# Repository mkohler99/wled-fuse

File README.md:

# wled-fuse
# WTF?
Happy holidays, If you're reading this the odds are you received one of my um, holiday cards? and have scanned the QR code on the back. This is some documentation for how to use WLED specifically in the context of this board.

# About WLED
WLED Is an open source RGB Pixel LED controller made by smart people on the internet. Information about the WLED project can be found here: [WLED Github Page](https://github.com/Aircoookie/WLED)
I make no claims about the reliability or color accuracy of WLED, however I think it's a really neat project and saved me having to even think about the software for this project (no thoughts, head empty, just solder LED and exist). WLED has some neat features that make it great for making fun LED toys. In no particular order:

 - Wifi Control with built in Web GUI
 - Built in controls and effects
 - Support for sACN (Referred to as E 1.31 for some reason)
 - Automatic wifi setup 

# How to connect
When the device boots, it attempts to connect to its last known wifi network. In most cases, when you first power up your board, it will not connect automatically. In this case, the board will create its own hotspot with the SSID **WLED-FUSE** 

in order to connect to the onboard hotspot, you will need to enter the default WLED password, **wled1234** you should then be automatically redirected to the WLED GUI which self hosts at **4.3.2.1** (which is a bit of a strange vanity IP, but I guess since they are the router they can do whatever they want)

You can use the device like this with its built in AP mode, but your phone may be weird about being connected to wifi that doesn't go anywhere, so you may want to connect the board to a real wifi network. 

# Wifi Setup

### To connect your WLED module to your home Wifi:

**1.**  Click on the  _Config_  (gear) icon to edit your WLED module settings and choose 'Wifi Setup'.

**2.**  For most home networks, simply enter your Wifi network's name and network password. You can also change the mDNS address for your WLED module here. By default, I've made it **fuse.local** so once your device is connected, you should just be able to enter that into your browser and you're off to the races. You can also 'Scan' for available networks and enter the password to any you find.

**3.**  Click Save & Connect at the top of the page.

**4.**  Reconnect your device to your home's Wifi network.

**5.**  Check the device list in your router's user interface for the IP of the WLED device within your local network. Alternatively, the device will advertise itself with mDNS as **fuse.local** so in theory, just enter that in your address bar and it should take you to the GUI. Failing that, use the WLED app (free on the App Store, as it is able to discover WLED boards without knowing the IP! Have fun with the WLED software!

# WLED Tips:
**1** Whatever is saved into preset 1 will load on boot, making the board's power up preset / effect customizable. 

**2** A visual list of WLED's built in FX can be found [here](https://kno.wled.ge/features/effects/)

**3** Multiple WLED boards can be synchronized together

# DMX Control
WLED is controllable using Artnet or Streaming ACN. Information on how to do that can be found [in the WLED documentation](https://kno.wled.ge/interfaces/e1.31-dmx/) Someone should make a DMX screen in d3 that implements its pixel map so it can be mapped from d3.

# WLED on your own
If you want to install WLED fresh, you can connect your board over USB-C to a computer and reinstall WLED from [this website](https://install.wled.me) which uses 'Web Serial' (which is a real web API for communicating with locally plugged in serial devices) to reprogram the board. It's WILD how easy they made this process. 

After flashing, only the 'F' will light up because WLED does not know about the other GPIO pins I used in my custom layout. As an exercise, I broke each letter out into its own 'pin' off the microcontroller [(Schematic for those interested)](https://github.com/mkohler99/wled-fuse/blob/main/Electronics/Drawings/Fuse%20LED%20Board%20Schematic.pdf), so in the LED settings you'll need to set up the following LED outputs:

 1. Pin 16 - 10 LEDs - Type WS281X - GRB
 2. Pin 17 - 10 LEDs - Type WS281X - GRB
 3. Pin 18 - 10 LEDs - Type WS281X - GRB
 4. Pin 19 - 11 LEDs - Type WS281X - GRB

Here's a screenshot of some of the settings

 **Fun Fact: The 'e' in the fuse logo has the most squares by one, with the logo in total made up of 41 squares, 4 being small, 11 being medium sized, and the remainder being large**

If you'd like to just reload my configuration file, you can find it linked [here.](https://github.com/mkohler99/wled-fuse/blob/main/Config/wled_cfg_fuse.json) You can upload a config file from the 'Security and Updates' tab at the bottom of the web GUI.
 
 # About this board
This board has a number of interesting features that were either complicated or expensive to implement, but were ultimately added in order to make the project more interesting

 - 3 Sizes of LEDs: In order to accurately replicate the FUSE logo, 3 sizes of RGB pixel LED's were used. Care was taken to use LED's that were electrically identical and because they speak the same protocol could be included in the same string of LEDs. Additional care was taken to find LEDs with built in decoupling capacitors. Older generations of LED pixels would require a capacitor soldered onto the board for each LED, but newer generations include this inside the LED. [Here is a link to a video of the factory of how these LEDs are made](https://www.youtube.com/watch?v=pMjhJ9kcaU4&pp=ygUOd3MyODEyIGZhY3Rvcnk=) finding the right features of LED's involved uploading Chinese part spec sheets into google translate and seeing if additional components were not needed as per the data sheets. An early LED test board was made to prove that different size LEDs could exist on the same data chain.

- 4 Layer board with all components on one side: This makes the boards easier to hand assemble and solder with a hotplate. The process is straightforward: Solder paste is applied with a stencil, Components are placed on the board (by hand!), the board is then heated on a hot plate to 165*C for about a minute and the solder liquifies and flows onto the pads of the components. Afterwards, a bit of touch up with a normal soldering iron is sometimes required (Usually on the USB connector)

- USB C Connector: This complicated things quite a bit, but since USB C is the future I wanted to prove that I could make a board that works over USB C. The pitch of the contacts is incredibly fine so even with care applying solder paste, shorts usually occur and needed to be cleaned up by hand, but I got way better at soldering these the more I did so mission successful there. An early LED test board was made to prove I was able to reliably solder this connector.
- In circuit programming: The board plugs into USB C and can be programmed with the default Platform IO IDE or the online WebSerial installer for WLED. There are no confusing boot/reset buttons because a clever array of transistors manage the proper logic for placing the chip into programming mode when the correct DTR/RTS pins on the serial port are used.  A more cost optimized version of this board would likely have an unpopulated header on the board that connects to an external programming device during flashing that is not included in the final product. An early LED test board was made to prove that I had this logic correct before committing to making boards with all the finished components.

# Mechanical
The included 3d printed stand easily attatches to the bottom like in this fancy rendering!

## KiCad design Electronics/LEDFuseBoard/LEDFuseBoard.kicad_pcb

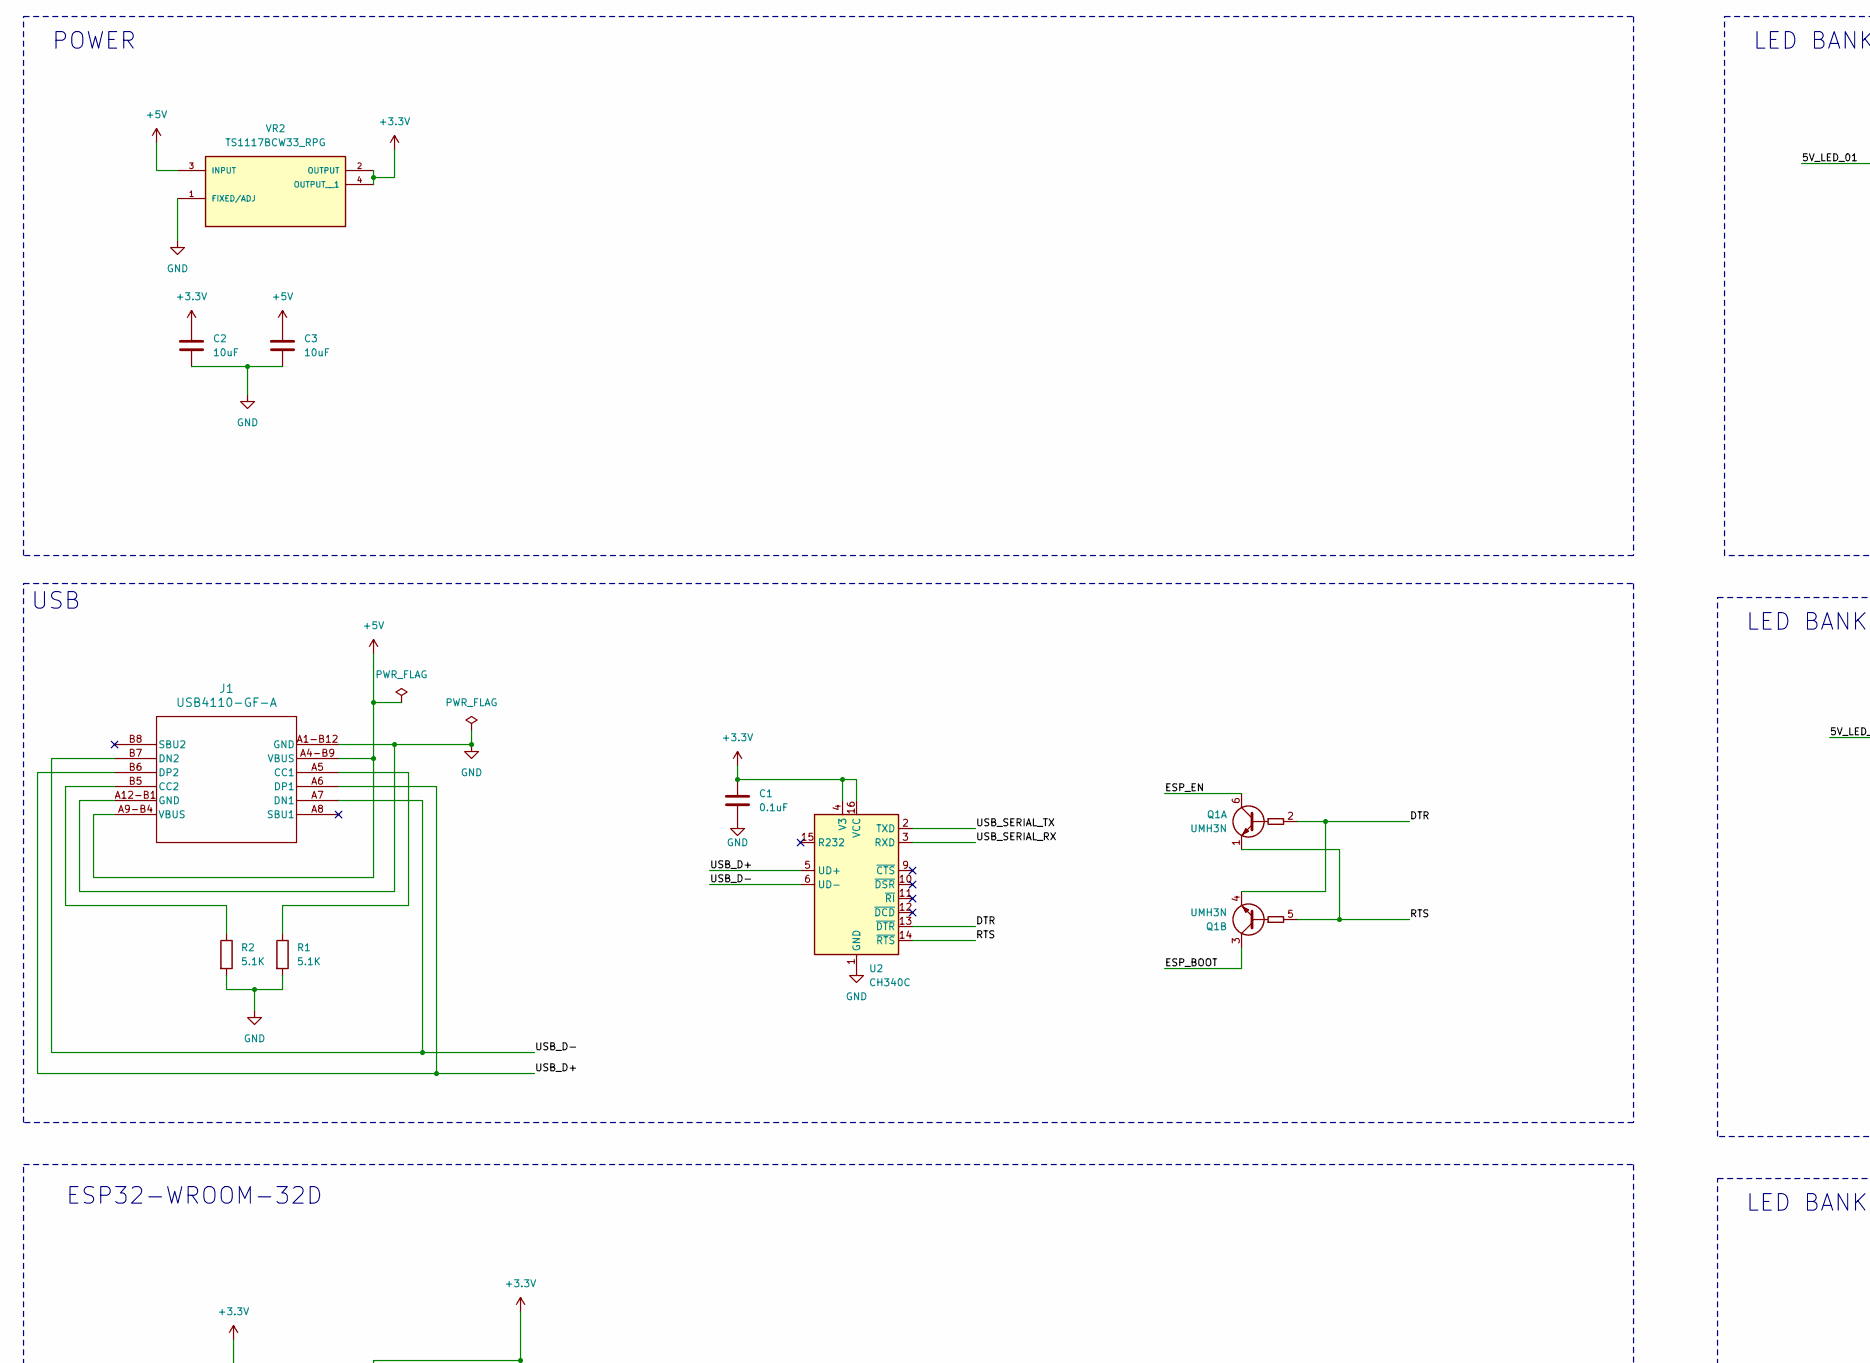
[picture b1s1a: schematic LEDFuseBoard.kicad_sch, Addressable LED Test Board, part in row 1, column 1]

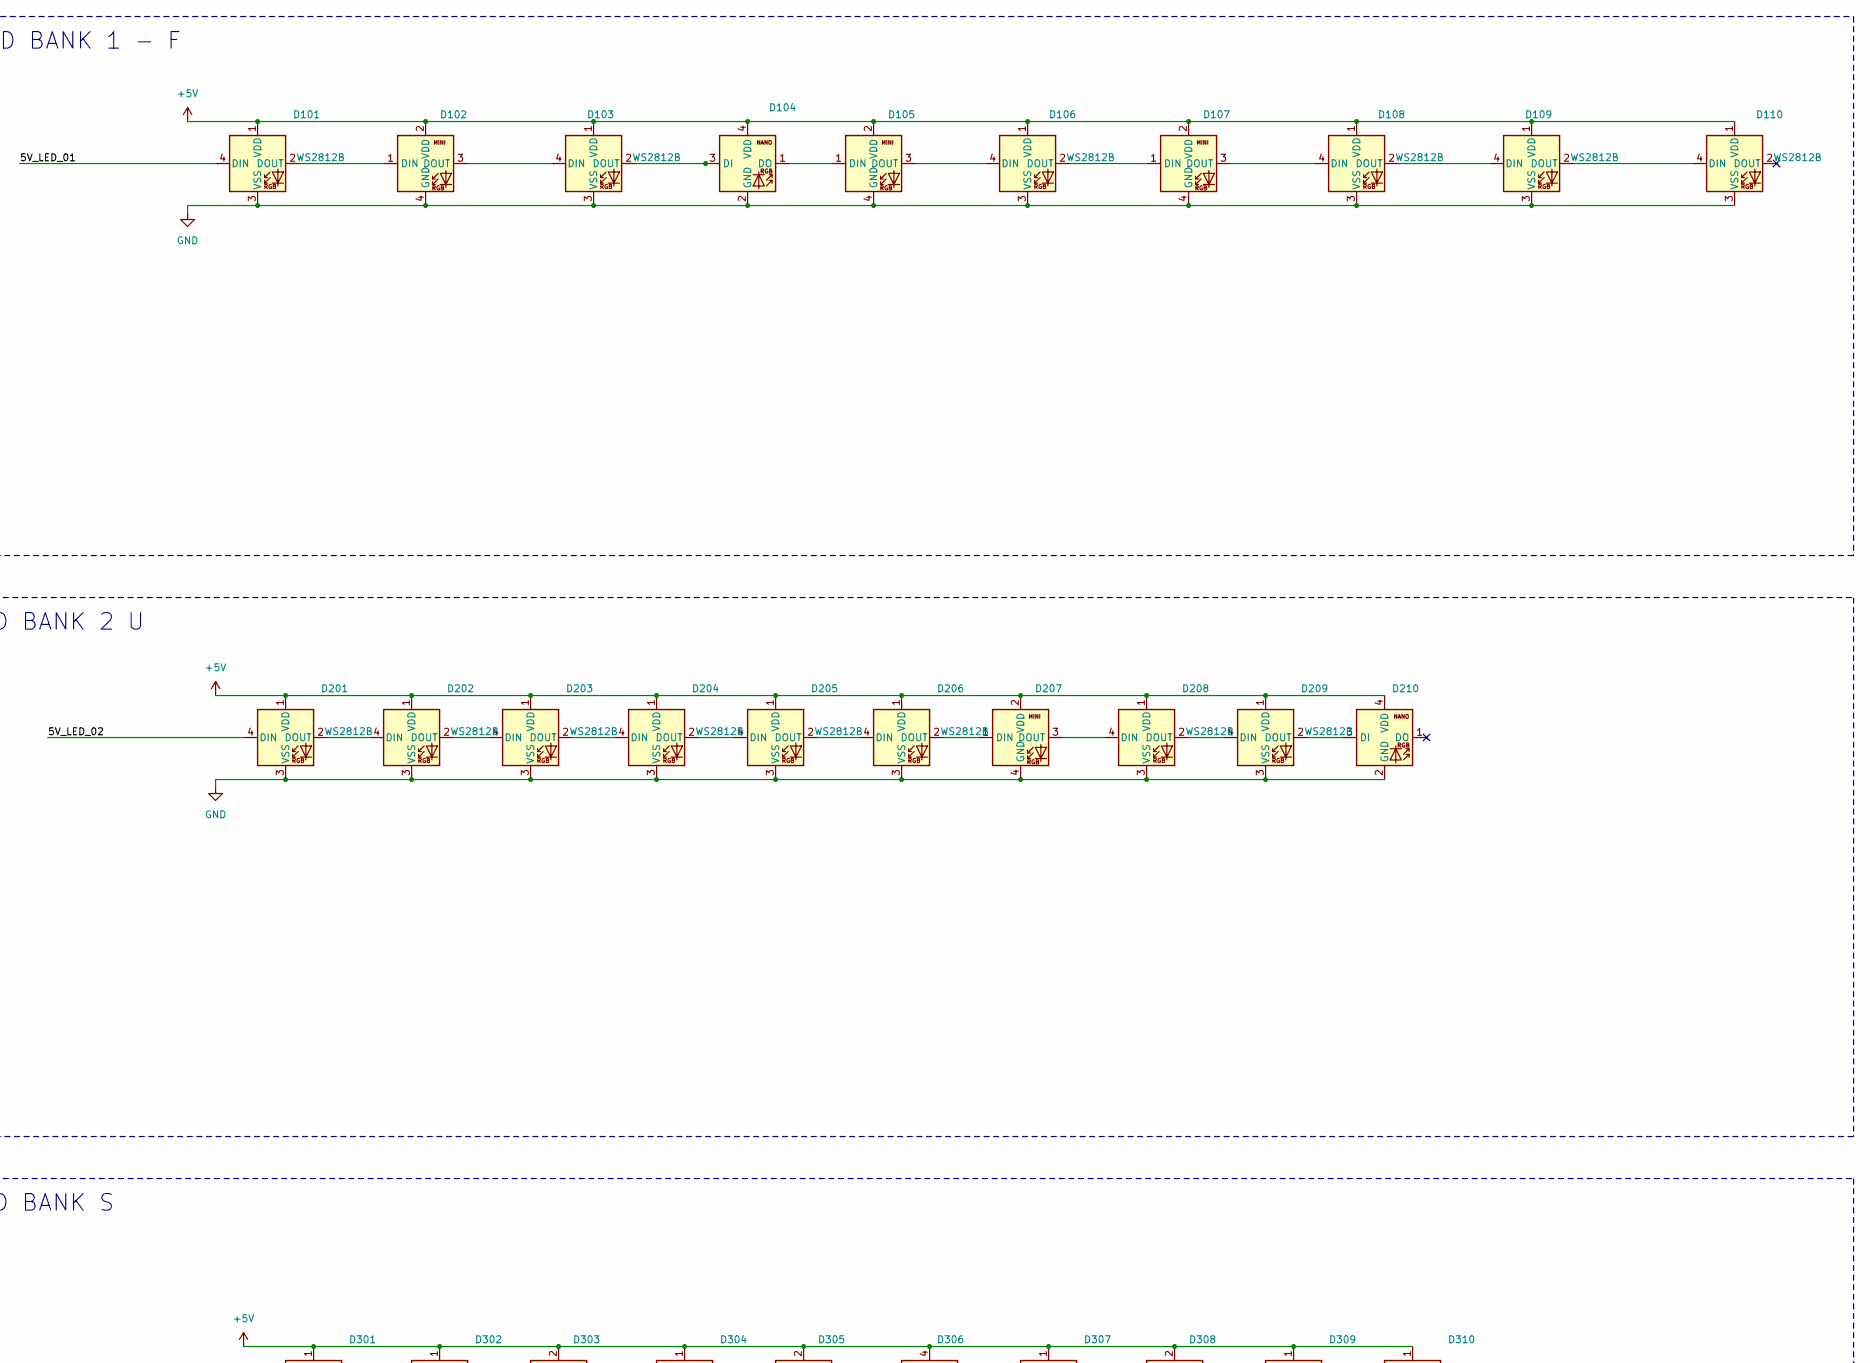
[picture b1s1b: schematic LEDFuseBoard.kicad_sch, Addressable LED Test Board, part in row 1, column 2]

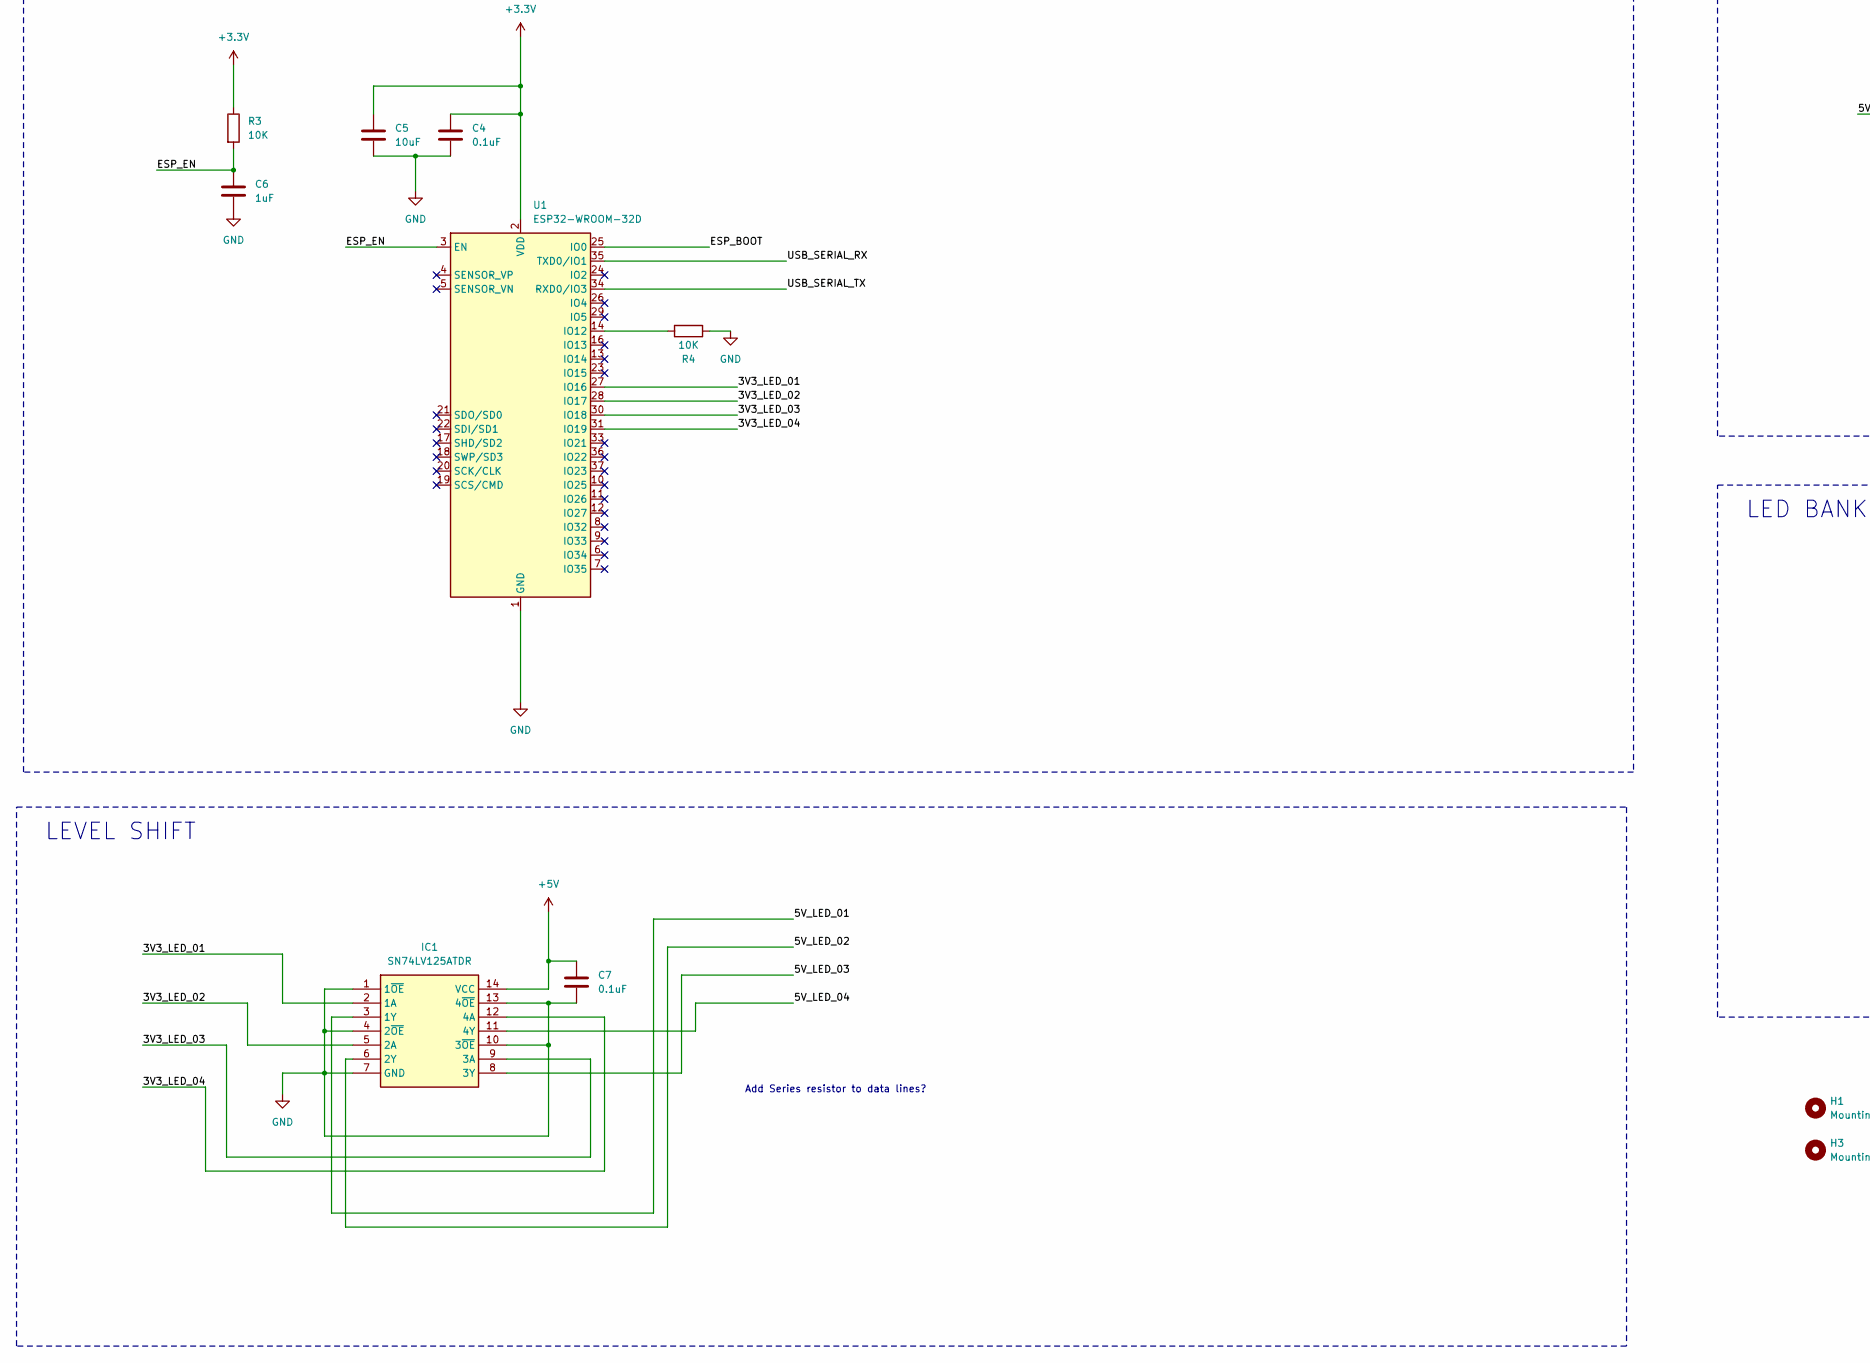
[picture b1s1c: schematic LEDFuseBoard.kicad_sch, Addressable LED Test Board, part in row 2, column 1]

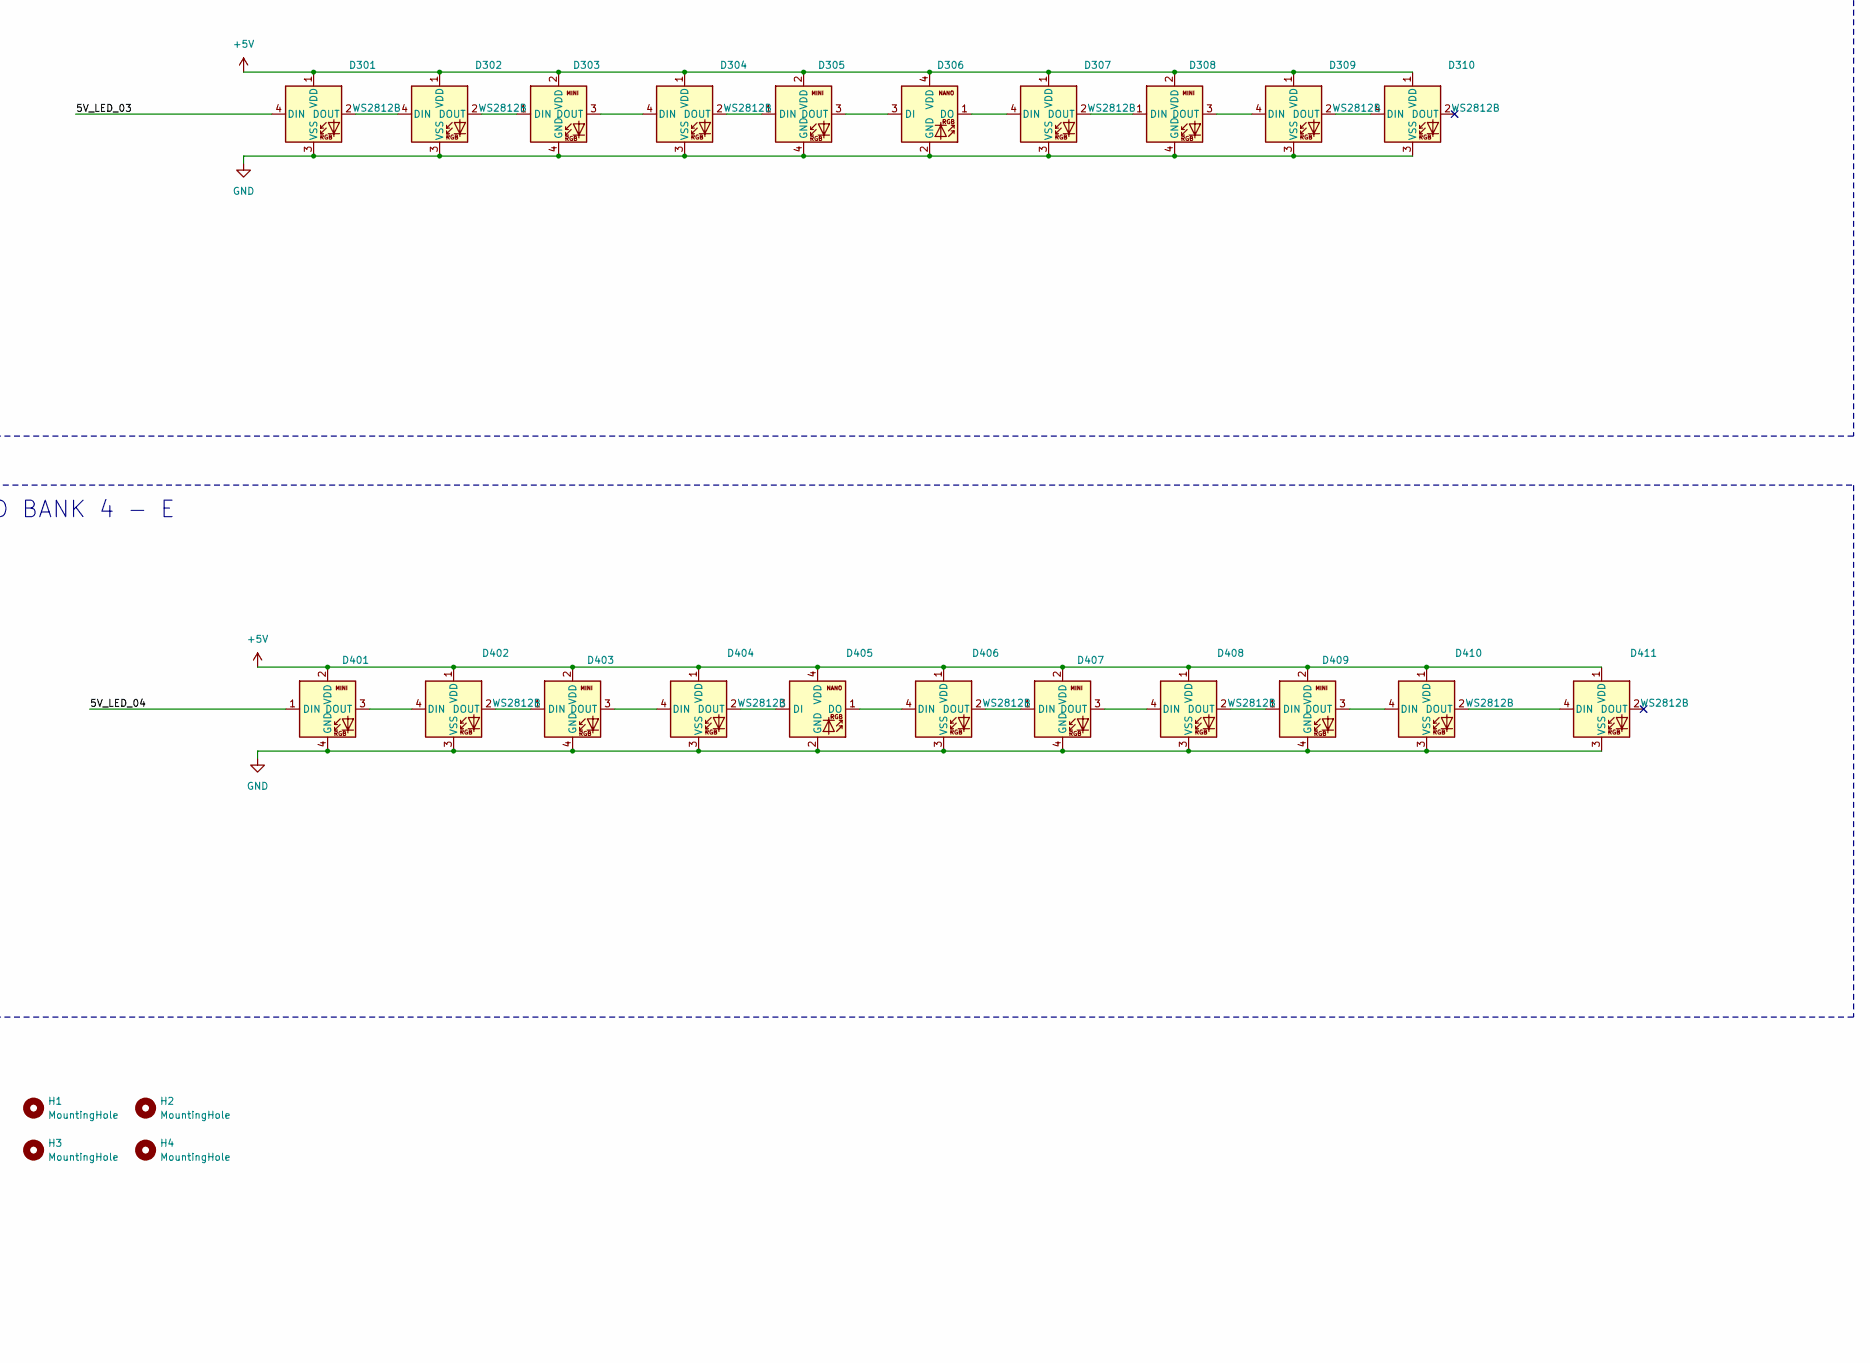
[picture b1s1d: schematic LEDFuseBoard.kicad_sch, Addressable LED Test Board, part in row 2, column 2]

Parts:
C1, C4, C7: 0.1uF; C_0805_2012Metric_Pad1.18x1.45mm_HandSolder
C2, C3, C5: 10uF; C_0805_2012Metric_Pad1.18x1.45mm_HandSolder
C6: 1uF; C_0805_2012Metric_Pad1.18x1.45mm_HandSolder
D101, D103, D106, D108, D109, D110, D201, D202, D203, D204, D205, D206, D208, D209, D301, D302, D304, D307, D309, D310, D402, D404, D406, D408, D410, D411: WS2812B; LED_WS2812B_PLCC4_5.0x5.0mm_P3.2mm
D102, D105, D107, D207, D303, D305, D308, D401, D403, D407, D409: WS2812MiniMK
D104, D210, D306, D405: LED_WS2812B-2020_PLCC4_2.0x2.0mm
H1, H2, H3, H4: MountingHole; MountingHole_3.2mm_M3
IC1: SN74LV125ATDR; SOIC127P600X175-14N; Mouser Part Number 595-SN74LV125ATDR
J1: USB4110-GF-A; USB4110-GF-A_GCT
Q1: UMH3N; SOT-363_SC-70-6
R1, R2: 5.1K; R_0805_2012Metric_Pad1.20x1.40mm_HandSolder
R3, R4: 10K; R_0805_2012Metric_Pad1.20x1.40mm_HandSolder
U1: ESP32-WROOM-32D
U2: CH340C; SOIC-16_3.9x9.9mm_P1.27mm
VR2: TS1117BCW33_RPG; VREG_TS1117BCW33_RPG; PARTREV H1607

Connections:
+3.3V: C1.1, C2.1, C4.1, C5.1, R3.1, U1.2 (VDD), U2.4 (V3), U2.16 (VCC), VR2.2 (OUTPUT), VR2.4 (OUTPUT__1)
+5V: C3.1, C7.1, D101.1 (VDD), D102.2 (VDD), D103.1 (VDD), D104.4 (VDD), D105.2 (VDD), D106.1 (VDD), D107.2 (VDD), D108.1 (VDD), D109.1 (VDD), D110.1 (VDD), D201.1 (VDD), D202.1 (VDD), D203.1 (VDD), D204.1 (VDD), D205.1 (VDD), D206.1 (VDD), D207.2 (VDD), D208.1 (VDD), D209.1 (VDD), D210.4 (VDD), D301.1 (VDD), D302.1 (VDD), D303.2 (VDD), D304.1 (VDD), D305.2 (VDD), D306.4 (VDD), D307.1 (VDD), D308.2 (VDD), D309.1 (VDD), D310.1 (VDD), D401.2 (VDD), D402.1 (VDD), D403.2 (VDD), D404.1 (VDD), D405.4 (VDD), D406.1 (VDD), D407.2 (VDD), D408.1 (VDD), D409.2 (VDD), D410.1 (VDD), D411.1 (VDD), IC1.14 (VCC), J1.A4-B9 (VBUS), J1.A9-B4 (VBUS), VR2.3 (INPUT)
/3V3_LED_01: IC1.2 (1A), U1.27 (IO16)
/3V3_LED_02: IC1.5 (2A), U1.28 (IO17)
/3V3_LED_03: IC1.9 (3A), U1.30 (IO18)
/3V3_LED_04: IC1.12 (4A), U1.31 (IO19)
/5V_LED_01: D101.4 (DIN), IC1.3 (1Y)
/5V_LED_02: D201.4 (DIN), IC1.6 (2Y)
/5V_LED_03: D301.4 (DIN), IC1.8 (3Y)
/5V_LED_04: D401.1 (DIN), IC1.11 (4Y)
/DTR: Q1.2 (B1), Q1.4 (E2), U2.13 (~DTR)
/ESP_BOOT: Q1.3 (C2), U1.25 (IO0)
/ESP_EN: C6.1, Q1.6 (C1), R3.2, U1.3 (EN)
/RTS: Q1.1 (E1), Q1.5 (B2), U2.14 (~RTS)
/USB_D+: J1.A6 (DP1), J1.B6 (DP2), U2.5 (UD+)
/USB_D-: J1.A7 (DN1), J1.B7 (DN2), U2.6 (UD-)
/USB_SERIAL_RX: U1.35 (TXD0/IO1), U2.3 (RXD)
/USB_SERIAL_TX: U1.34 (RXD0/IO3), U2.2 (TXD)
GND: C1.2, C2.2, C3.2, C4.2, C5.2, C6.2, C7.2, D101.3 (VSS), D102.4 (GND), D103.3 (VSS), D104.2 (GND), D105.4 (GND), D106.3 (VSS), D107.4 (GND), D108.3 (VSS), D109.3 (VSS), D110.3 (VSS), D201.3 (VSS), D202.3 (VSS), D203.3 (VSS), D204.3 (VSS), D205.3 (VSS), D206.3 (VSS), D207.4 (GND), D208.3 (VSS), D209.3 (VSS), D210.2 (GND), D301.3 (VSS), D302.3 (VSS), D303.4 (GND), D304.3 (VSS), D305.4 (GND), D306.2 (GND), D307.3 (VSS), D308.4 (GND), D309.3 (VSS), D310.3 (VSS), D401.4 (GND), D402.3 (VSS), D403.4 (GND), D404.3 (VSS), D405.2 (GND), D406.3 (VSS), D407.4 (GND), D408.3 (VSS), D409.4 (GND), D410.3 (VSS), D411.3 (VSS), IC1.1 (1~OE), IC1.4 (2~OE), IC1.7 (GND), IC1.10 (3~OE), IC1.13 (4~OE), J1.A1-B12 (GND), J1.A12-B1 (GND), R1.2, R2.2, R4.1, U1.1 (GND), U1.15 (GND), U1.38 (GND), U1.39 (GND), U2.1 (GND), VR2.1 (FIXED/ADJ)
unnamed: D101.2 (DOUT), D102.1 (DIN)
unnamed: D102.3 (DOUT), D103.4 (DIN)
unnamed: D103.2 (DOUT), D104.3 (DI)
unnamed: D104.1 (DO), D105.1 (DIN)
unnamed: D105.3 (DOUT), D106.4 (DIN)
unnamed: D106.2 (DOUT), D107.1 (DIN)
unnamed: D107.3 (DOUT), D108.4 (DIN)
unnamed: D108.2 (DOUT), D109.4 (DIN)
unnamed: D109.2 (DOUT), D110.4 (DIN)
unnamed: D201.2 (DOUT), D202.4 (DIN)
unnamed: D202.2 (DOUT), D203.4 (DIN)
unnamed: D203.2 (DOUT), D204.4 (DIN)
unnamed: D204.2 (DOUT), D205.4 (DIN)
unnamed: D205.2 (DOUT), D206.4 (DIN)
unnamed: D206.2 (DOUT), D207.1 (DIN)
unnamed: D207.3 (DOUT), D208.4 (DIN)
unnamed: D208.2 (DOUT), D209.4 (DIN)
unnamed: D209.2 (DOUT), D210.3 (DI)
unnamed: D301.2 (DOUT), D302.4 (DIN)
unnamed: D302.2 (DOUT), D303.1 (DIN)
unnamed: D303.3 (DOUT), D304.4 (DIN)
unnamed: D304.2 (DOUT), D305.1 (DIN)
unnamed: D305.3 (DOUT), D306.3 (DI)
unnamed: D306.1 (DO), D307.4 (DIN)
unnamed: D307.2 (DOUT), D308.1 (DIN)
unnamed: D308.3 (DOUT), D309.4 (DIN)
unnamed: D309.2 (DOUT), D310.4 (DIN)
unnamed: D401.3 (DOUT), D402.4 (DIN)
unnamed: D402.2 (DOUT), D403.1 (DIN)
unnamed: D403.3 (DOUT), D404.4 (DIN)
unnamed: D404.2 (DOUT), D405.3 (DI)
unnamed: D405.1 (DO), D406.4 (DIN)
unnamed: D406.2 (DOUT), D407.1 (DIN)
unnamed: D407.3 (DOUT), D408.4 (DIN)
unnamed: D408.2 (DOUT), D409.1 (DIN)
unnamed: D409.3 (DOUT), D410.4 (DIN)
unnamed: D410.2 (DOUT), D411.4 (DIN)
unnamed: J1.A5 (CC1), R1.1
unnamed: J1.B5 (CC2), R2.1
unnamed: R4.2, U1.14 (IO12)

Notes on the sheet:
USB
LED BANK 1 - F
LED BANK S
Add Series resistor to data lines?
ESP32-WROOM-32D
LED BANK 4 - E
LEVEL SHIFT
LED BANK 2 U
POWER

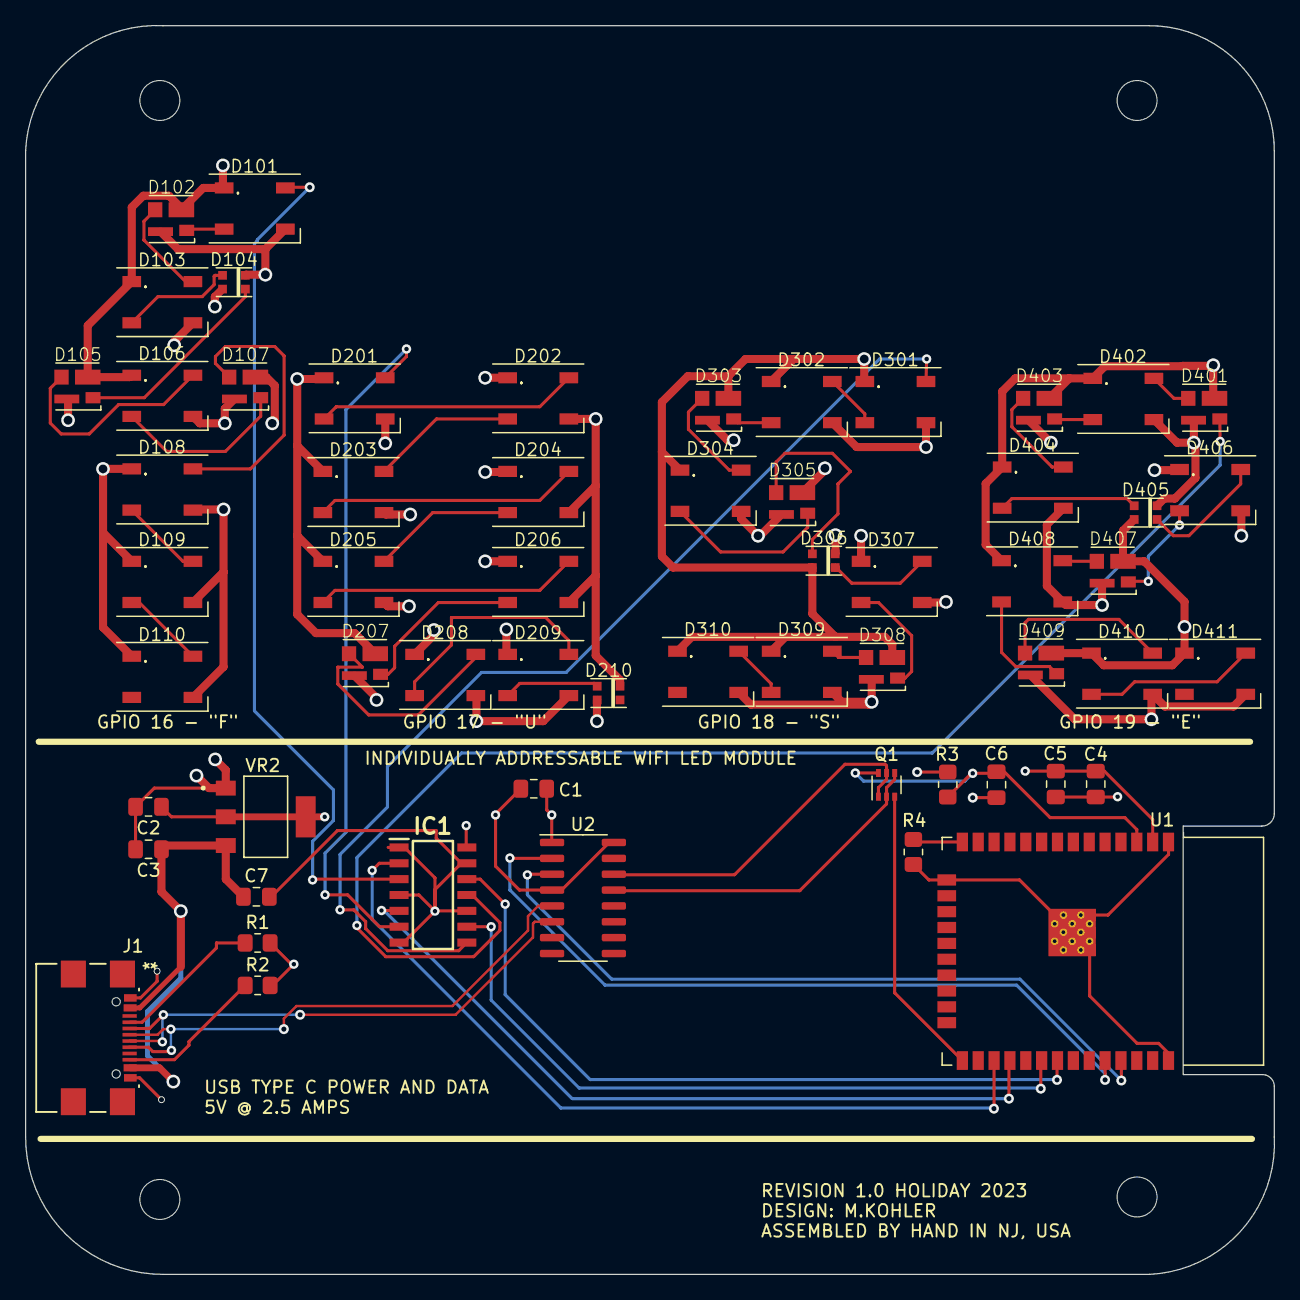
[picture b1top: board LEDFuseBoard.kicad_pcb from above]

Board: 4 copper layers, 100.0 x 100.0 mm, 62 parts (0 on the bottom side), 59 nets.

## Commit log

2023-11-26 Initial Commit of design files
